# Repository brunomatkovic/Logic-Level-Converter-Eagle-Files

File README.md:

# Logic Level Converter Eagle Files
## Image

## Description and details
If you've ever tried to use 3.3V device inside 5V system, you know how complicated it can be. This Bi-directional logic level converter steps down 5V signals to 3.3V and steps up 3.3V signals to 5V at the same time. It can also work with 2.8V and 1.8V devices. This device has a capability of converting 4 pins of the high side to 4 pins of the low side with 2 inputs and 2 outputs provided for both sides.

Using this converter ain't a problem. Board needs to be powered from 2 voltage sources (high and low voltage) that your system is using. For example, 5V to HV, 3.3V to LV and system's ground to GND pin.
## Repository content
This repo contains Cadsoft Eagle .sch and .brd files for Logic Level Converter board. Files have been arranged into folders for navigating between different versions of board. Tip: layer 200 shows top silkscreen and layer 208 should be bottom silkscreen. tParts and bParts is not used.

## Docs
* [Logic Level Converter product page] ( )

## Board versions
* v1.0 - initial version

## License info
This product is open-source. Yay! For any tech questions, contact us at [techsupport@e-radionica.com](techsupport@e-radionica.com) If you find an Issue, please open one at GitHub. If you can improve our product, fork us.

e-radionica.com Team.

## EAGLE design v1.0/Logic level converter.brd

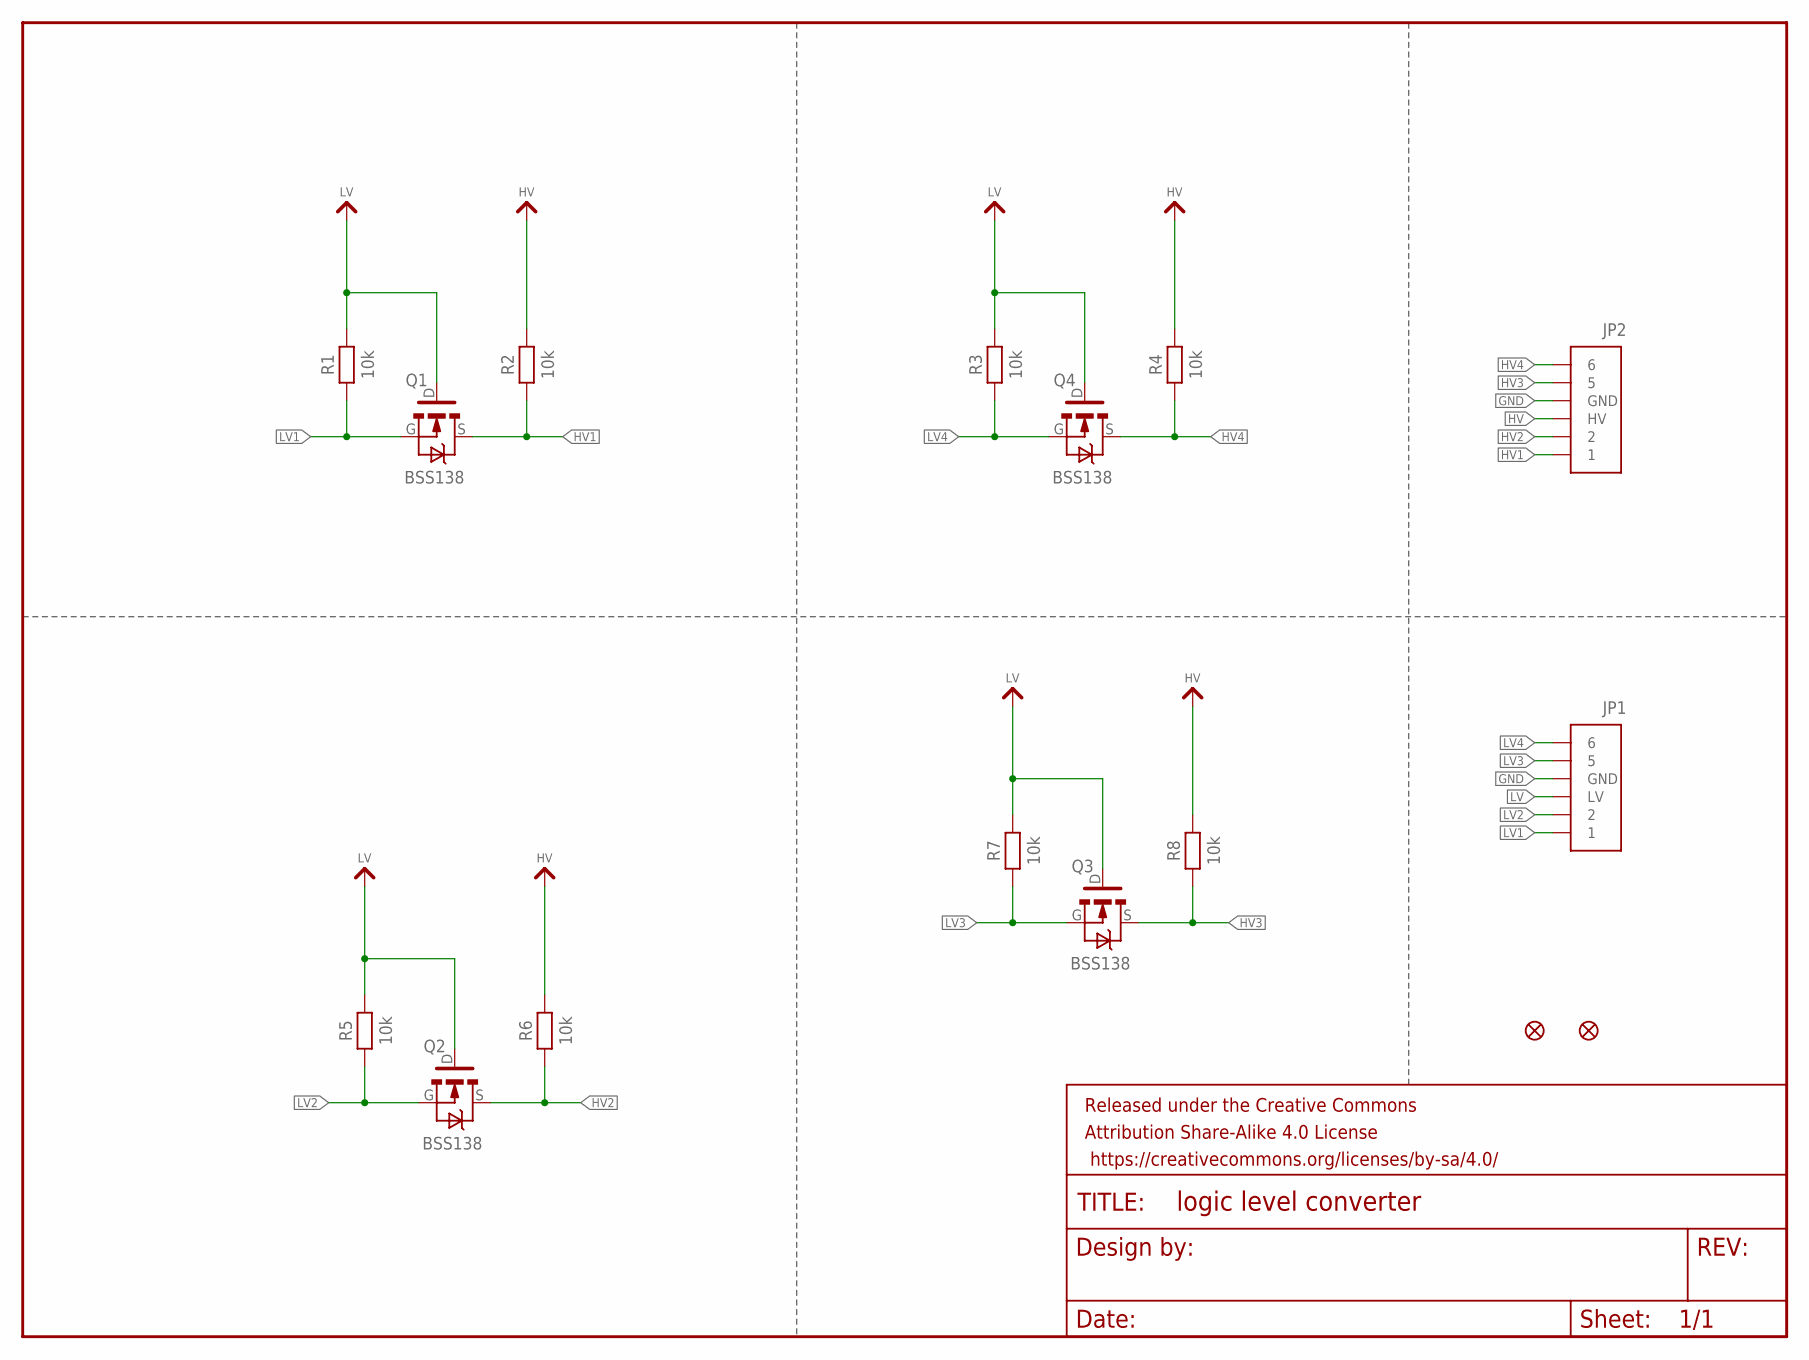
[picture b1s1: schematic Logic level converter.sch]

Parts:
FD1: FIDUCIAL1X2; FIDUCIAL-1X2
FD2: FIDUCIALUFIDUCIAL; FIDUCIAL-MICRO
FRAME1: FRAME-LETTERNO_PACKAGE; DUMMY
JP1: JUMPER_6PIN_LLC_LV
JP2: JUMPER_6PIN_LLC_HV
Q1, Q2, Q3, Q4: BSS138; SOT-23
R1, R2, R3, R4, R5, R6, R7, R8: 10k; 0603_RESISTOR

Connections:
GND: JP1.GND, JP2.GND
HV: JP2.HV, R2.P$2, R4.P$2, R6.P$2, R8.P$2
HV1: JP2.1, Q1.S, R2.P$1
HV2: JP2.2, Q2.S, R6.P$1
HV3: JP2.5, Q3.S, R8.P$1
HV4: JP2.6, Q4.S, R4.P$1
LV: JP1.LV, Q1.D, Q2.D, Q3.D, Q4.D, R1.P$2, R3.P$2, R5.P$2, R7.P$2
LV1: JP1.1, Q1.G, R1.P$1
LV2: JP1.2, Q2.G, R5.P$1
LV3: JP1.5, Q3.G, R7.P$1
LV4: JP1.6, Q4.G, R3.P$1

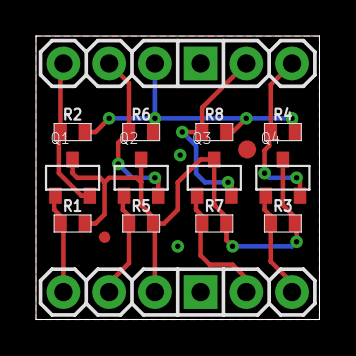
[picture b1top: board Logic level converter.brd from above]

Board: 2 copper layers, 15.8 x 15.8 mm, 20 parts (0 on the bottom side), 11 nets.

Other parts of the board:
E$1: E-R.IO-BACK-6MM
E$3: OSH-BACK-3MM
E$4: LOGO-BACK-3MM

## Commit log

2018-08-24 Adding to Github
    adding version folder, adding eagle files

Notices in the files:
parts and their libraries:
SparkFun-Aesthetics: Licensing: Creative Commons ShareAlike 4.0 International - https://creativecommons.org/licenses/by-sa/4.0
SparkFun-Aesthetics: Released under the Creative Commons Attribution Share-Alike 4.0 License
SparkFun-Aesthetics: https://creativecommons.org/licenses/by-sa/4.0
